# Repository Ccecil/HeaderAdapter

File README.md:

This board is meant to be used with the Gadgeteer pinout to convert into "standard" 2.54 pinheaders.
Intended for use with the V2 Smoothieboard but should work with any standard gadgeteer header pinout.

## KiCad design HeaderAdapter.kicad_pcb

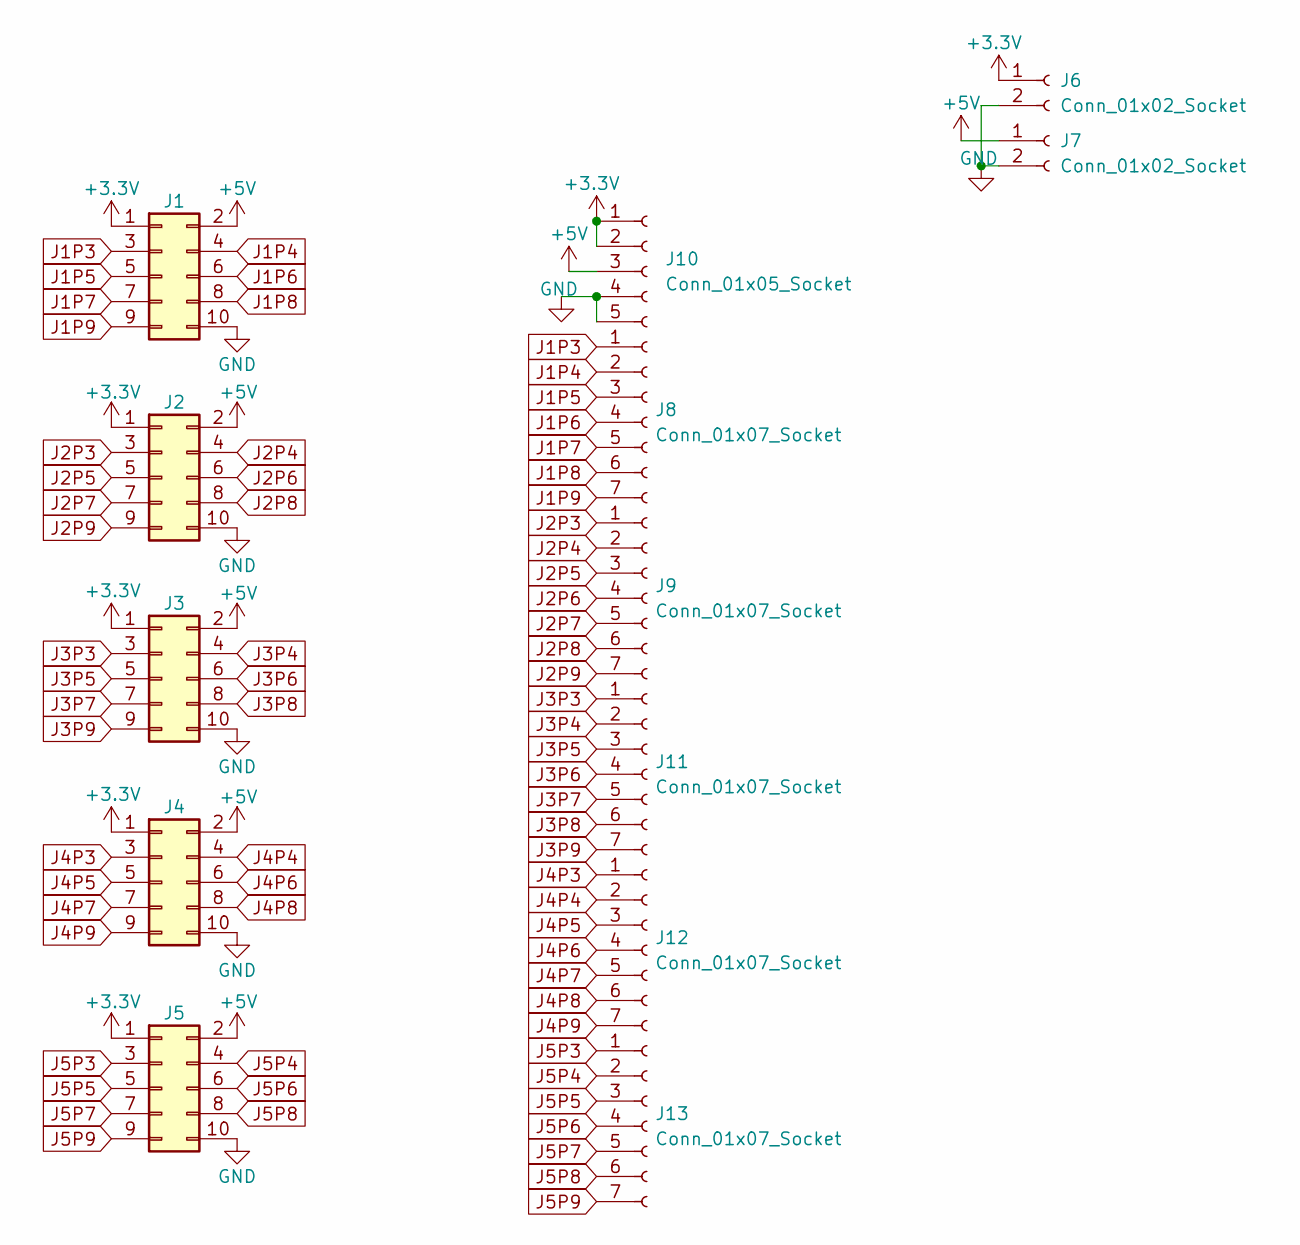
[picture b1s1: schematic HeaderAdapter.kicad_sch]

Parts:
J1, J2, J3, J4, J5: Conn_02x05_Odd_Even; PinHeader_2x05_P1.27mm_Vertical_SMD
J6, J7: Conn_01x02_Socket; JST_XH_B2B-XH-A_1x02_P2.50mm_Vertical
J8, J9, J11, J12, J13: Conn_01x07_Socket; PinSocket_1x07_P2.54mm_Vertical
J10: Conn_01x05_Socket; PinSocket_1x05_P2.54mm_Vertical

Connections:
+3.3V: J1.1, J2.1, J3.1, J4.1, J5.1, J6.1, J10.1, J10.2; also elsewhere on the board
+5V: J1.2, J2.2, J3.2, J4.2, J5.2, J7.1, J10.3; also elsewhere on the board
GND: J1.10, J2.10, J3.10, J4.10, J5.10, J6.2, J7.2, J10.4, J10.5; also elsewhere on the board
J1P3: J1.3, J8.1
J1P4: J1.4, J8.2
J1P5: J1.5, J8.3
J1P6: J1.6, J8.4
J1P7: J1.7, J8.5
J1P8: J1.8, J8.6
J1P9: J1.9, J8.7
J2P3: J2.3, J9.1
J2P4: J2.4, J9.2
J2P5: J2.5, J9.3
J2P6: J2.6, J9.4
J2P7: J2.7, J9.5
J2P8: J2.8, J9.6
J2P9: J2.9, J9.7
J3P3: J3.3, J11.1
J3P4: J3.4, J11.2
J3P5: J3.5, J11.3
J3P6: J3.6, J11.4
J3P7: J3.7, J11.5
J3P8: J3.8, J11.6
J3P9: J3.9, J11.7
J4P3: J4.3, J12.1
J4P4: J4.4, J12.2
J4P5: J4.5, J12.3
J4P6: J4.6, J12.4
J4P7: J4.7, J12.5
J4P8: J4.8, J12.6
J4P9: J4.9, J12.7
J5P3: J5.3, J13.1
J5P4: J5.4, J13.2
J5P5: J5.5, J13.3
J5P6: J5.6, J13.4
J5P7: J5.7, J13.5
J5P8: J5.8, J13.6
J5P9: J5.9, J13.7

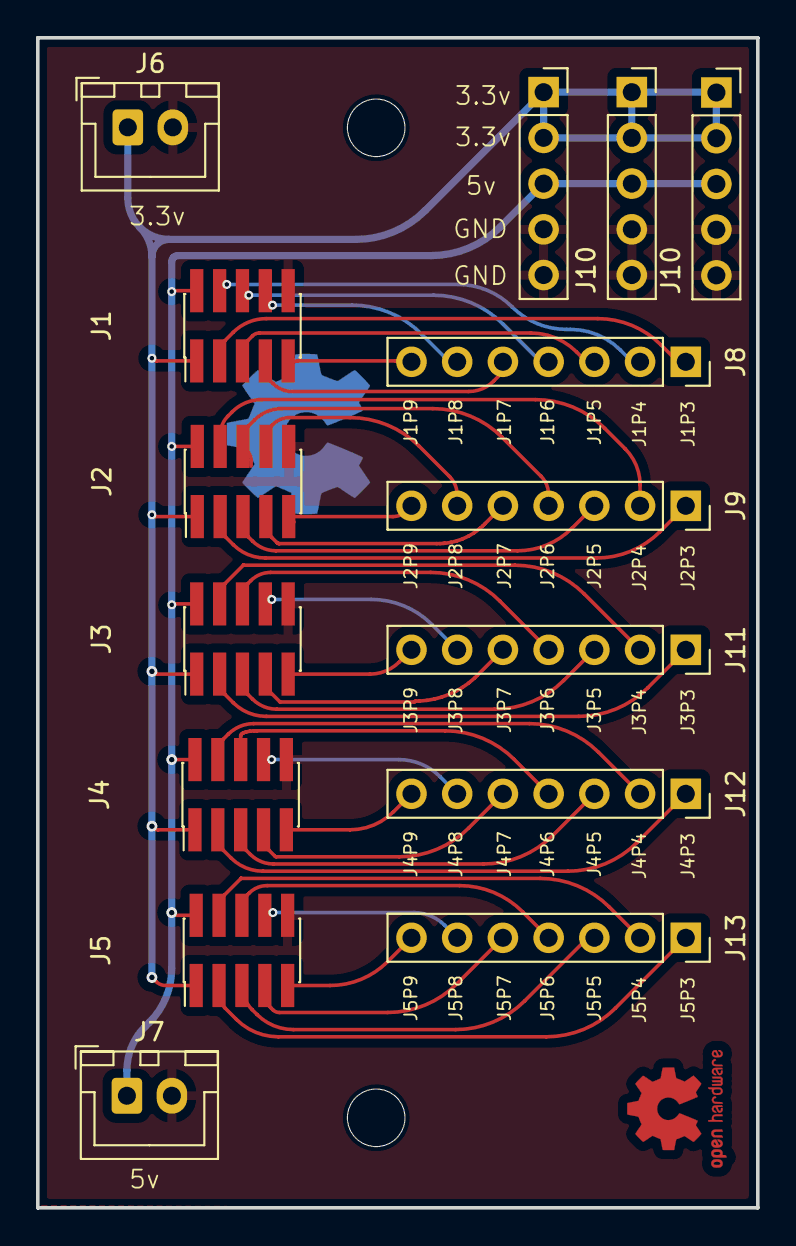
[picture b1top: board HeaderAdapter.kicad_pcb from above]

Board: 2 copper layers, 40.0 x 65.0 mm, 15 parts (0 on the bottom side), 38 nets.

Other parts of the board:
J10#2, J10#3: Conn_01x05_Socket; PinSocket_1x05_P2.54mm_Vertical

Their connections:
+3.3V: J10#2.1, J10#2.2, J10#3.1, J10#3.2; also elsewhere on the board
+5V: J10#2.3, J10#3.3; also elsewhere on the board
GND: J10#2.4, J10#2.5, J10#3.4, J10#3.5; also elsewhere on the board

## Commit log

2024-04-20 Initial upload of v0.1
